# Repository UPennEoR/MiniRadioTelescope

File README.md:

# Mini Radio Telescope

A computerized telescope created using a satellite TV dish and hobbyist electronic components.<br/>
This GitHub contains Arduino and Python code for the telescope.

## Hardware
### Electronics

* Satellite Dish (with LNB)
* Arduino Uno
* Raspberry Pi
* [Stepper Motors](https://www.sparkfun.com/products/13656)
* [Big Easy Driver](https://www.sparkfun.com/products/12859)

### RF
* [Bias Tee](https://www.minicircuits.com/WebStore/dashboard.html?model=ZFBT-282-1.5A%2B)
* [Lumped LC High Pass Filter, 910 - 3000 MHz](https://www.minicircuits.com/WebStore/dashboard.html?model=SHP-900%2B)
* [LTCC Low Pass Filter, DC - 1200 MHz, 50Ω](https://www.minicircuits.com/WebStore/dashboard.html?model=VLF-1200%2B)
* [Power Detector](https://www.minicircuits.com/WebStore/dashboard.html?model=ZX47-60LN-S%2B)
* [Low Noise Amplifier, 40 - 2600 MHz, 50Ω](https://www.minicircuits.com/WebStore/dashboard.html?model=ZX60-P105LN%2B)
* [RTL-SDR](https://www.amazon.com/RTL-SDR-Blog-RTL2832U-Software-Defined/dp/B0129EBDS2/)

[Detailed Parts List](https://docs.google.com/spreadsheets/d/1V9u7jmuFzU5uZdgKm3iKv23dL2x4DQUVWW0j8lXsqZ8/edit?usp=sharing)

## Maps

As of 5 April 2020, the working Arduino sketch is: MRTArduino (previously known as MRTv2)<br/>
The python code for the Pi is MRT_PY4.py

Hackaday was kind enough to do a write-up about this project: https://hackaday.com/2019/10/22/a-miniature-radio-telescope-in-every-backyard/

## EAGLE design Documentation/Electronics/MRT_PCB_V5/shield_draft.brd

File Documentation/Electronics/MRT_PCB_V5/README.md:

The zip file is appropriate for PCB4U.

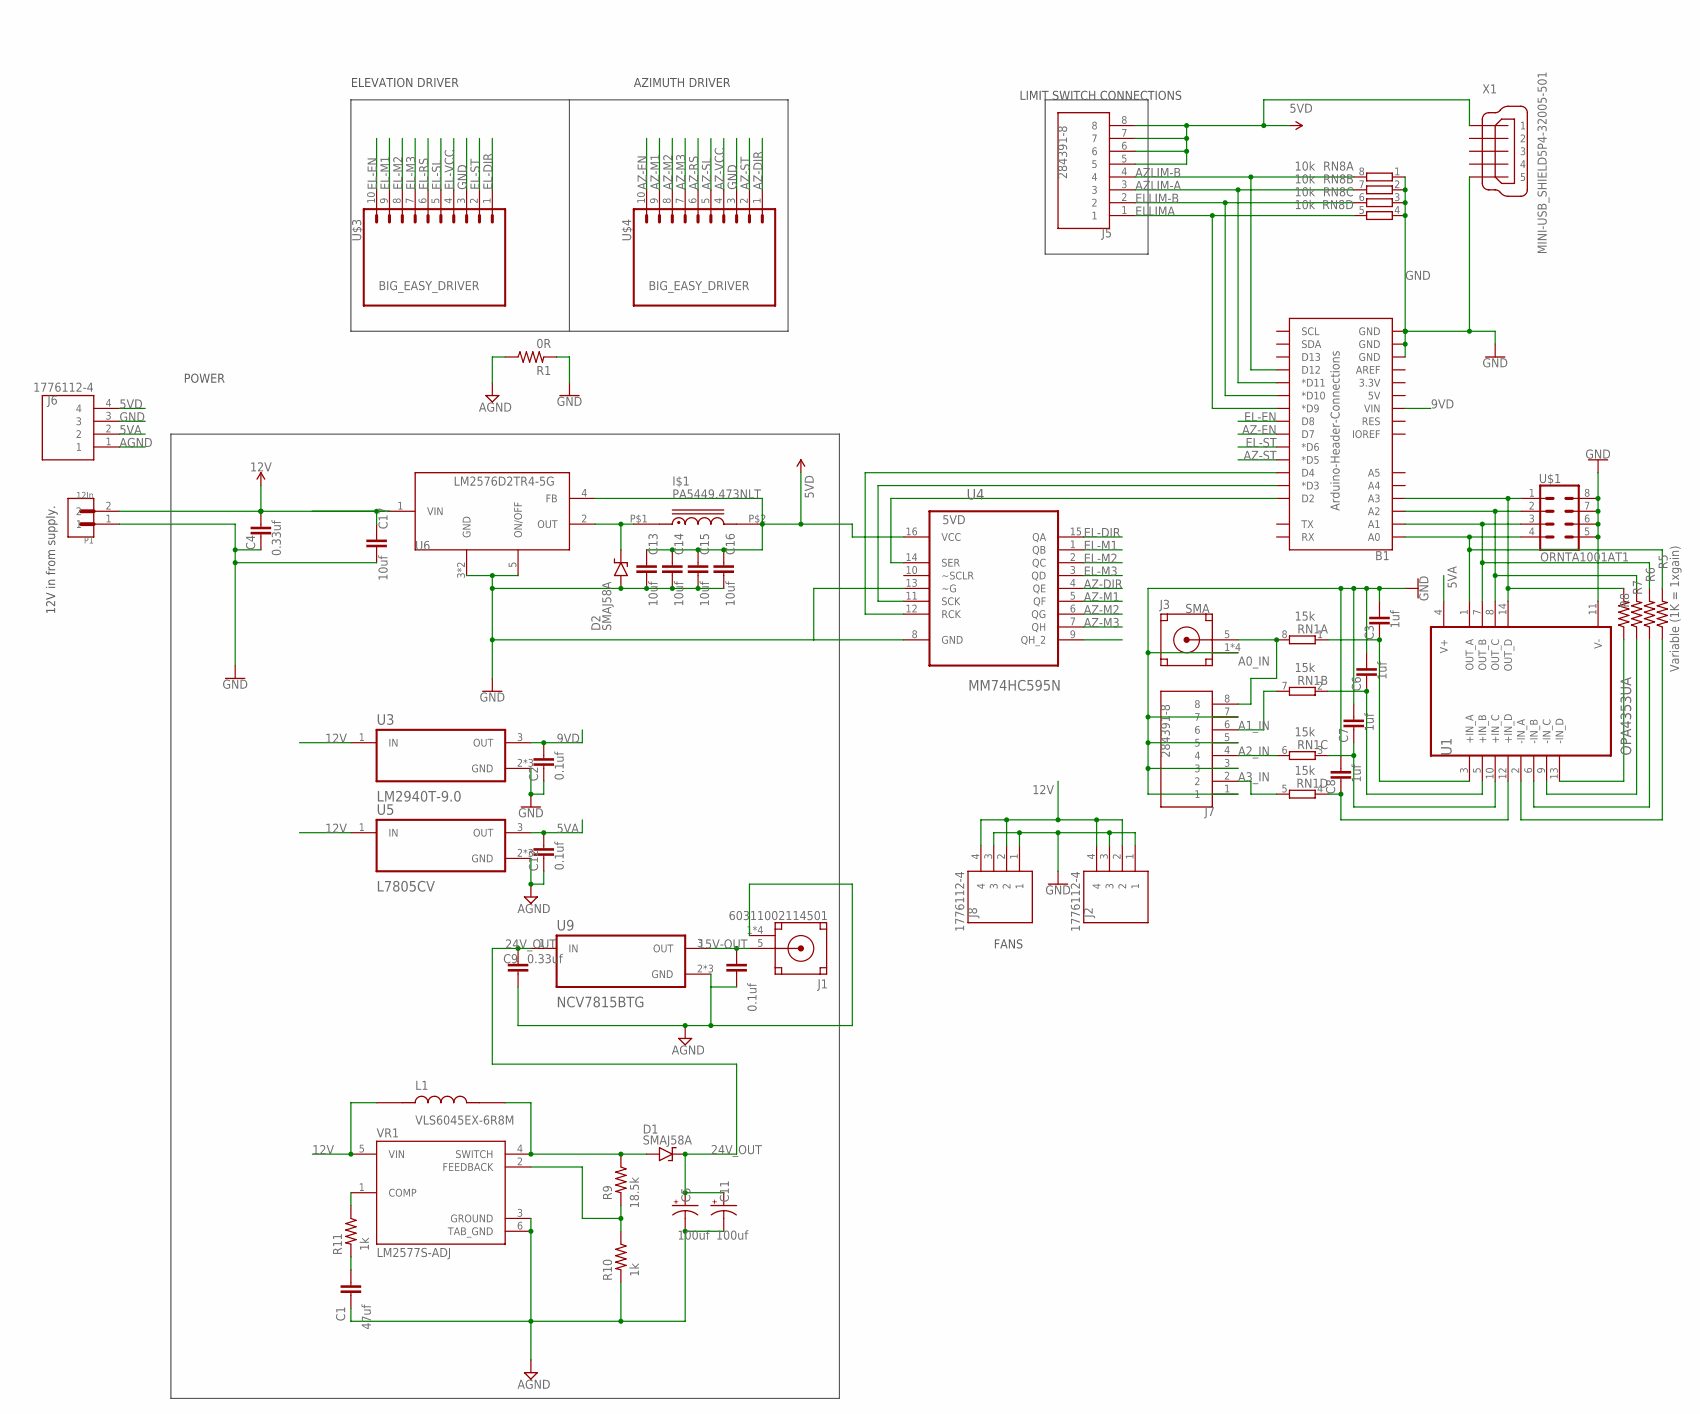
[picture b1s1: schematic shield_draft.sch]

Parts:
B1: Arduino-Header-Connections; UNO_R3_SHIELD
C1: 47uf; CAP_0805
C2, C10, C12: 0.1uf; CAP_0805
C3, C6, C7, C8: 1uf; CAP_0805
C4, C9: 0.33uf; CAP_0805
C5, C11: 100uf; E5-10,5
C13, C14, C15, C16, C17: 10uf; 0805
D1, D2: SMAJ58A; SMA
I$1: PA5449.473NLT; IND_TYS4020470M-10
J1: 60311002114501
J2, J6, J8: 1776112-4; TE_1776112-4
J3: SMA; 60311002114501
J5, J7: 284391-8; TE_284391-8
L1: VLS6045EX-6R8M; IND_VLS6045EX-6R8M
P1: 12In; OST_OSTTE020104
R1: 0R; 0603
R5: Variable (1K = 1xgain); RESAD1176W63L850D250B
R6, R7, R8: Var; RESAD1176W63L850D250B
R9: 18.5k; 0603
R10, R11: 1k; 0603
RN1: 15k; CAY16
RN8: 10k; CAY16
U1: OPA4353UA; SOIC127P600X175-14N
U3: LM2940T-9.0; TO254P1054X470X1955-3
U4: MM74HC595N; DIP254P762X533-16
U5: L7805CV; TO254P1054X470X1955-3
U6: LM2576D2TR4-5G; D2PAK-5
U9: NCV7815BTG; TO254P1054X470X1955-3
U$1: ORNTA1001AT1; SOIC127P600X175-8N
U$3, U$4: BIG_EASY_DRIVER; EASY_DRIVER_FTPRT
VR1: LM2577S-ADJ; TO170P1524X483-6N
X1: MINI-USB_SHIELD5P4-32005-501; 32005-501

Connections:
5VA: C12.2, J6.2, U1.4 (V+), U5.3 (OUT)
5VD: C13.1, C14.1, C15.1, C16.1, I$1.P$2 (2), J5.5, J5.6, J5.7, J5.8, J6.4, U4.16 (VCC), U6.4 (FB), X1.1
9VD: B1.VIN, C2.2, U3.3 (OUT)
12V: C4.2, C17.1, J2.2, J2.4, J8.2, J8.4, L1.1, P1.2, U3.1 (IN), U5.1 (IN), U6.1 (VIN), VR1.5 (VIN)
15V-OUT: C10.2, J1.5 (SIGNAL), U9.3 (OUT)
24V_OUT: C5.+, C9.2, C11.+, D1.C, U9.1 (IN)
24V_PRE: D1.A, L1.2, R9.1, VR1.4 (SWITCH)
A0_IN: J3.5 (SIGNAL), J7.8, RN1.8 (2)
A1_IN: J7.6, RN1.7 (2)
A2_IN: J7.4, RN1.6 (2)
A3_IN: J7.2, RN1.5 (2)
AGND: C1.1, C5.-, C9.1, C10.1, C11.-, C12.1, J1.1 (GND), J1.2 (GND), J1.3 (GND), J1.4 (GND), J6.1, R1.1, R10.2, U5.2 (GND), U5.P$1 (GND), U5.P$2 (GND), U9.2 (GND), U9.P$1 (GND), U9.P$2 (GND), VR1.3 (GROUND), VR1.6 (TAB_GND)
AIN+: C3.1, RN1.1, U1.3 (+IN_A)
AIN-: R5.1, U1.2 (-IN_A)
AZ-DIR: U4.4 (QE), U$4.1
AZ-EN: B1.D7, U$4.10
AZ-M1: U4.5 (QF), U$4.9
AZ-M2: U4.6 (QG), U$4.8
AZ-M3: U4.7 (QH), U$4.7
AZ-RS: U$4.6
AZ-SL: U$4.5
AZ-ST: B1.D5 (*D5), U$4.2
AZ-VCC: U$4.4
AZLIM-A: B1.D11 (*D11), J5.3, RN8.7 (2)
AZLIM-B: B1.D12, J5.4, RN8.8 (2)
A_OUT: B1.A0, R5.2, U1.1 (OUT_A), U$1.4 (R4A)
BIN+: C6.1, RN1.2 (1), U1.5 (+IN_B)
BIN-: R6.1, U1.6 (-IN_B)
B_OUT: B1.A1, R6.2, U1.7 (OUT_B), U$1.3 (R3A)
CIN+: C7.1, RN1.3 (1), U1.10 (+IN_C)
CIN-: R7.1, U1.9 (-IN_C)
C_OUT: B1.A2, R7.2, U1.8 (OUT_C), U$1.2 (R2A)
DIN+: C8.1, RN1.4 (1), U1.12 (+IN_D)
DIN-: R8.1, U1.13 (-IN_D)
D_OUT: B1.A3, R8.2, U1.14 (OUT_D), U$1.1 (R1A)
EL-DIR: U4.15 (QA), U$3.1
EL-EN: B1.D8, U$3.10
EL-M1: U4.1 (QB), U$3.9
EL-M2: U4.2 (QC), U$3.8
EL-M3: U4.3 (QD), U$3.7
EL-RS: U$3.6
EL-SL: U$3.5
EL-ST: B1.D6 (*D6), U$3.2
EL-VCC: U$3.4
ELLIM-B: B1.D10 (*D10), J5.2, RN8.6 (2)
ELLIMA: B1.D9 (*D9), J5.1, RN8.5 (2)
GND: B1.GND@0 (GND), B1.GND@1 (GND), B1.GND@2 (GND), C2.1, C3.2, C4.1, C6.2, C7.2, C8.2, C13.2, C14.2, C15.2, C16.2, C17.2, D2.A, J2.1, J2.3, J3.1 (GND), J3.2 (GND), J3.3 (GND), J3.4 (GND), J6.3, J7.1, J7.3, J7.5, J7.7, J8.1, J8.3, P1.1, R1.2, RN8.1, RN8.2 (1), RN8.3 (1), RN8.4 (1), U1.11 (V-), U3.2 (GND), U3.P$1 (GND), U3.P$2 (GND), U4.8 (GND), U4.13 (~G), U6.3 (GND), U6.5 (ON/OFF), U6.6 (GND), U$1.5 (R4B), U$1.6 (R3B), U$1.7 (R2B), U$1.8 (R1B), U$3.3, U$4.3, X1.5
unnamed: B1.D2, U4.14 (SER)
unnamed: R9.2, R10.1, VR1.2 (FEEDBACK)
unnamed: D2.C, I$1.P$1 (1), U6.2 (OUT)
unnamed: R11.1, VR1.1 (COMP)
unnamed: C1.2, R11.2
unnamed: B1.D3 (*D3), U4.11 (SCK)
unnamed: B1.D4, U4.12 (RCK)

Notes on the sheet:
POWER
ELEVATION DRIVER
AZIMUTH DRIVER
LIMIT SWITCH CONNECTIONS
12V in from supply.
FANS

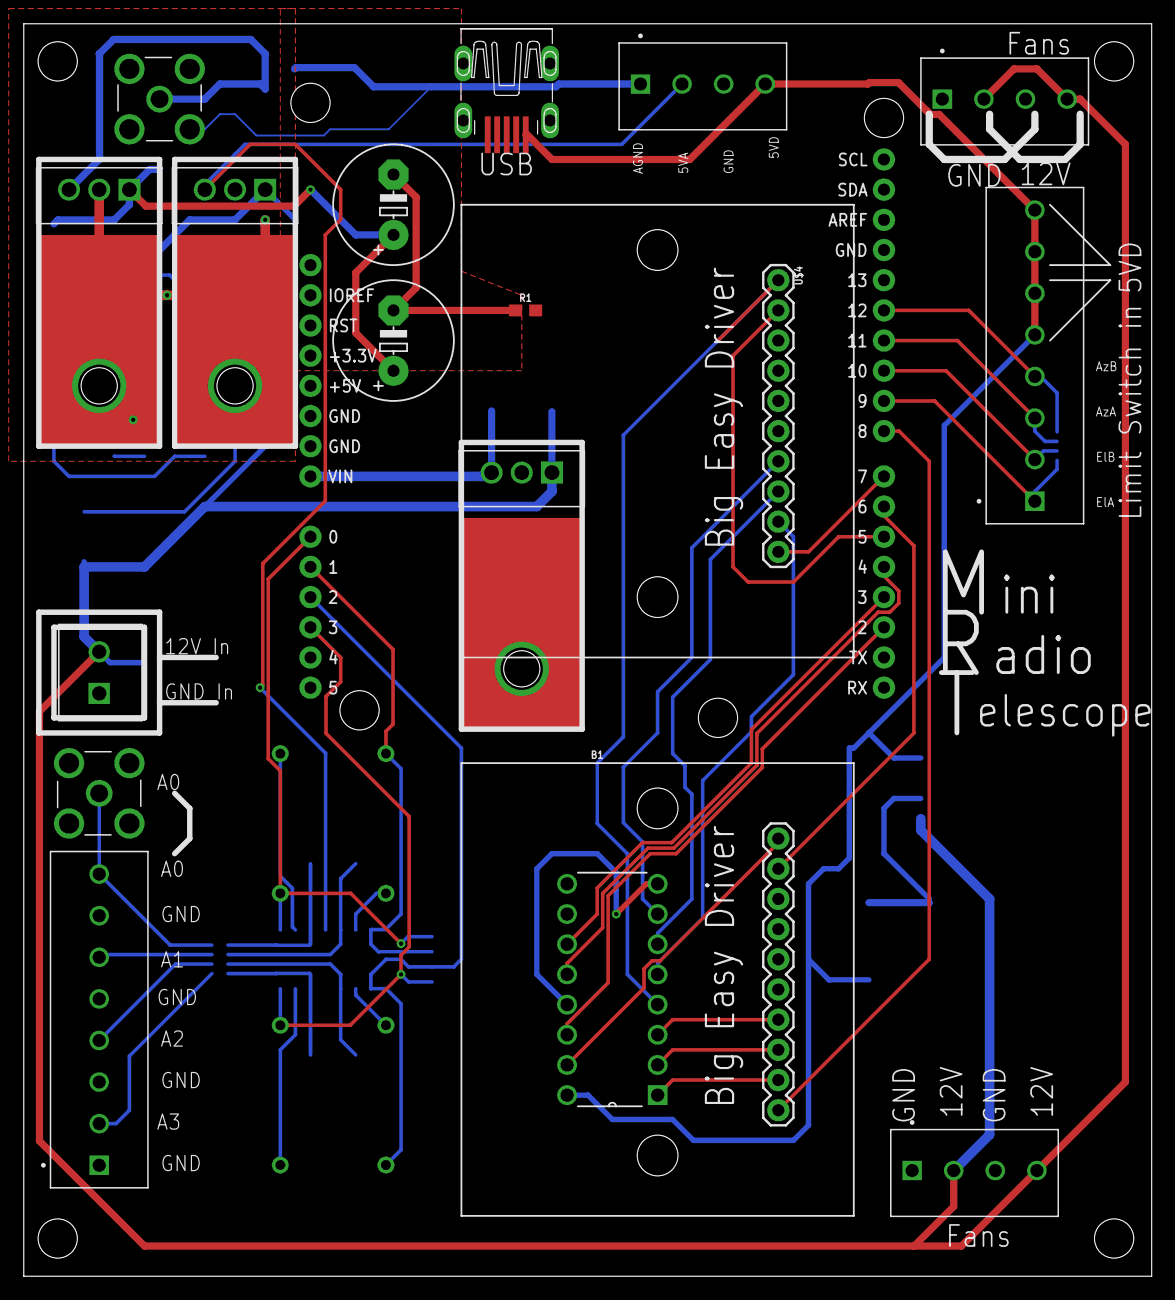
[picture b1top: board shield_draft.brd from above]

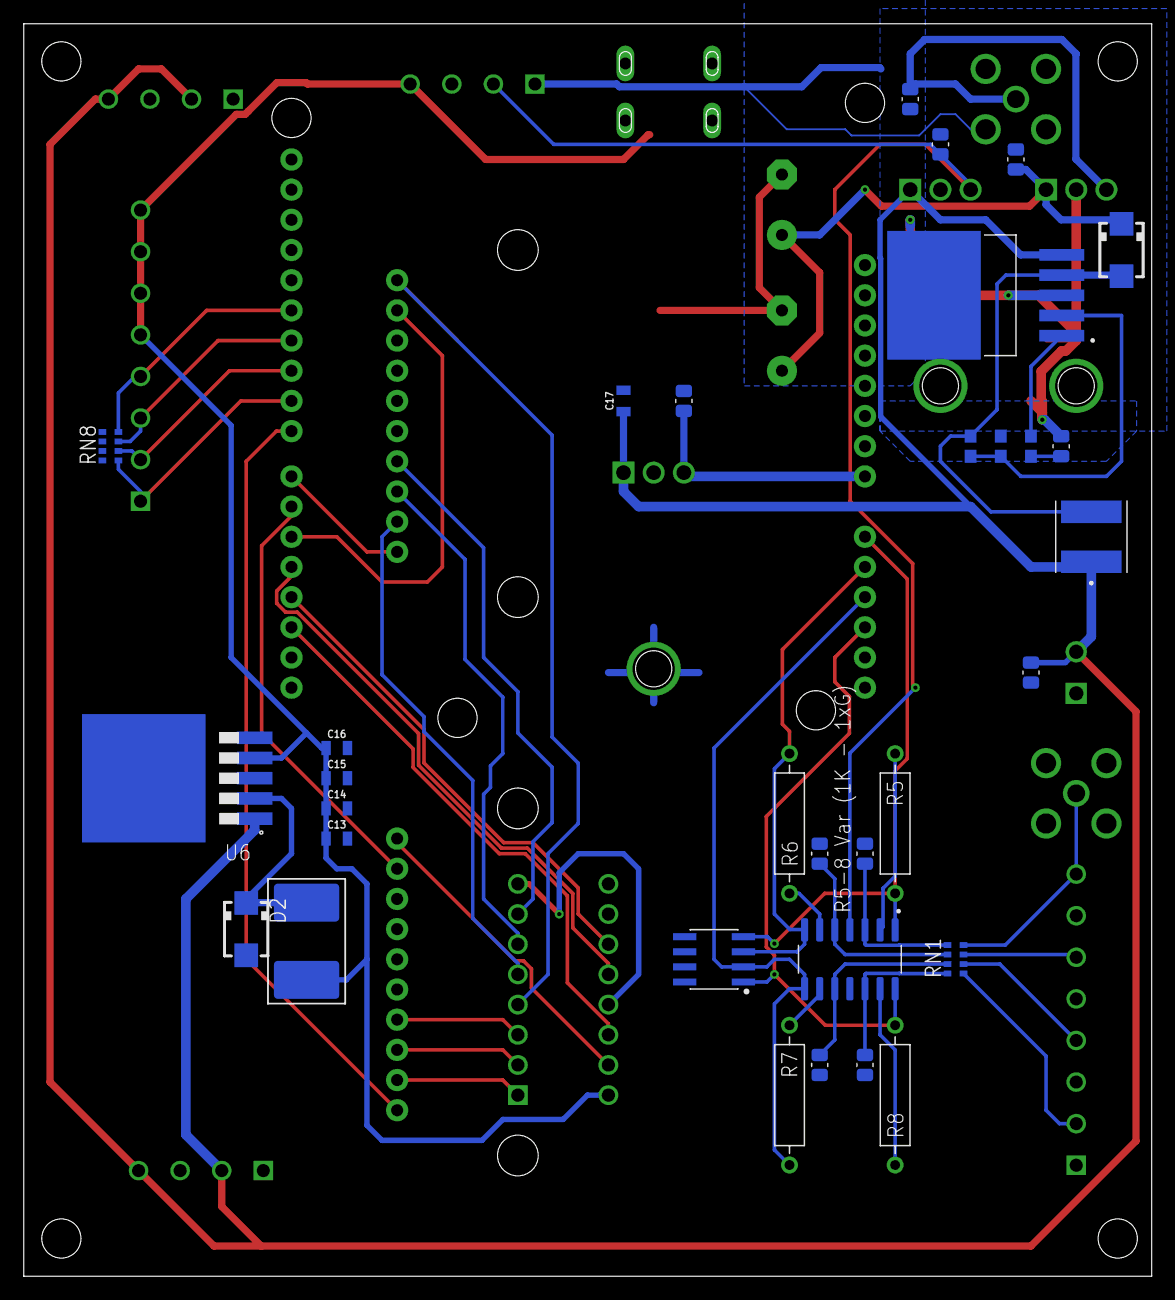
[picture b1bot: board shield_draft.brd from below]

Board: 2 copper layers, 94.9 x 105.4 mm, 59 parts (32 on the bottom side), 48 nets.

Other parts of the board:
JP1, JP2, JP3, JP4, JP5, JP6, JP7, JP10: STAND-OFF

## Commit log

2016-07-15 Arduino code for the LMS9DS1 sensor and separately for motor control
2016-07-18 Real time plotting
2016-07-18 Trying to make a python version of the Arduino serial monitor
2016-07-20 pyArduinoSerialTerminal.py basically reproduces the Arduino Serial Monitor functionality now, though there is a bit of an offset between when the Arduino sends something to the buffer and this progra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
2016-07-29 Serial communication
2016-07-29 A serial communication tester for Arduino
2016-07-29 Working simple serial communication with Arduino
2016-08-10 Making the Arduino stuff more organized
2016-08-10 One more Arduino ino
2016-08-10 Pseudo-working Arduino and Python serial
2016-08-15 added a test of handshaking
2016-08-16 handshaking example
2016-08-26 serial communication now working with Pi
2016-12-14 Adding some documentation
2016-12-14 Current working version
2017-02-09 Thu Feb 9 16:56:14 EST 2017
2017-02-09 unbroken version
2017-03-01 Wed Mar 1 14:04:58 EST 2017
2017-03-01 Wed Mar 1 17:38:22 EST 2017
2017-03-03 Fri Mar 3 10:53:11 EST 2017
2017-03-28 Tue Mar 28 00:14:23 EDT 2017
2017-04-01 Sat Apr 1 10:40:33 EDT 2017
2017-06-21 Wed Jun 21 14:34:22 EDT 2017
2017-06-30 Fri Jun 30 14:20:31 EDT 2017
2017-06-30 Fri Jun 30 14:43:24 EDT 2017
2017-06-30 Fri Jun 30 14:46:32 EDT 2017
2017-07-05 Wed Jul 5 10:19:24 EDT 2017
2017-07-07 Fri Jul 7 15:49:47 EDT 2017
2017-07-07 Fri Jul 7 15:54:09 EDT 2017
2017-07-09 Sun Jul 9 14:03:56 EDT 2017
2017-07-18 Tue Jul 18 13:09:20 EDT 2017
2017-07-28 Fri Jul 28 11:50:43 EDT 2017
2017-08-01 Notes on Pi3 installation
2017-08-07 Installation instructions
2017-08-07 rtlsdr_scan.py
2017-08-08 Tue Aug 8 16:58:33 EDT 2017
2017-08-08 Tue Aug 8 17:03:22 EDT 2017
2017-08-09 Shell script way of starting MRTControl.py
2017-08-09 Wed Aug 9 09:54:37 EDT 2017
2017-08-09 Wed Aug 9 11:14:17 EDT 2017
2017-08-09 Wed Aug 9 11:16:30 EDT 2017
2017-08-09 An example SDR spectrum
2017-08-10 Wed Aug 9 21:29:55 EDT 2017
2017-10-12 Thu Oct 12 16:13:34 EDT 2017
2017-10-26 Committing.
2017-11-17 Adding a new version of the MRT software
2017-11-17 Fri Nov 17 17:44:08 EST 2017
2017-11-17 Fri Nov 17 18:33:53 EST 2017
2017-11-17 Fri Nov 17 18:43:14 EST 2017
2017-11-27 Mon Nov 27 02:38:42 EST 2017
2017-12-03 Sun Dec 3 11:36:05 EST 2017
2017-12-04 Mon Dec 4 01:33:33 EST 2017
2017-12-04 Mon Dec 4 11:17:35 EST 2017
2017-12-04 Mon Dec 4 11:25:31 EST 2017
2017-12-04 Mon Dec 4 18:47:03 EST 2017
2018-01-16 Tue Jan 16 10:54:02 EST 2018
2018-04-04 Wed Apr 4 09:42:31 EDT 2018
2018-04-04 Wed Apr 4 09:58:07 EDT 2018
2018-04-04 Wed Apr 4 11:13:50 EDT 2018
2018-04-11 Wed Apr 11 13:49:21 EDT 2018
2018-04-12 Thu Apr 12 12:15:35 EDT 2018
2018-04-27 Fri Apr 27 19:12:53 EDT 2018
2018-04-28 Fri Apr 27 20:41:38 EDT 2018
2018-04-28 Fri Apr 27 20:52:47 EDT 2018
2018-05-14 Mon May 14 15:30:04 EDT 2018
2018-06-11 Adding PCRT design document
2018-06-13 Made a new version for a python3 compatible MRT.py
2018-06-14 should be working
2018-06-15 Fri Jun 15 12:29:36 EDT 2018
2018-06-15 Fri Jun 15 12:35:22 EDT 2018
2018-06-15 Trying to get satellites with MRT
2018-06-15 Getting them satellites
2018-06-15 Adding maps
2018-06-15 the maps
2018-06-19 Tuesday June 19 update
2018-06-19 the maps 2
2018-07-03 All mrt functions
2018-07-03 temporary MRT PY3 to sort functions into a new file
2018-07-03 new file containing information on the state of the telescope
2018-07-03 New file containing just the opening for the program from opening the port to initializing the state
2018-07-03 test file for mrt func, doesn't contain every function that func does
2018-07-06 seems to be working, no longer producesnone type nonsubscriptable error
2018-07-06 also seems to be working, about to input while loop that runs MRT
2018-07-06 holds the state
2018-07-06 funcional by itself, but having problems in tandem with FUNC
2018-07-06 Fully functional up to the GoTo function
2018-07-09 Almost fully functional, just need to work out the bugs caused by the mapping funcions in FUNC
2018-07-09 WE ARE SO CLOSE! Just need to work on the bugs in mapping functions to accomodate changes in how scan and goto and state work
2018-07-12 Everything seems to be functional, just cleaning up a bit and adding features now.
2018-07-12 Fully functional
2018-07-12 fully functional now, but the official program is MRT_PY3.py which is the same as this one.
2018-07-12 Finally no bugs, works great.
2018-07-12 Fully functional with some new modifications, including variable dimensions in mapping and a print menu function.
2018-07-12 Still fully functional, just working on cleaning up the figures produced by the mapping functions.
2018-07-16 added some stuff, cleaned up the code, and added comments to everything for better understanding
2018-07-16 Nothing new, just a little cleaner.
2018-07-23 A few tweeks and things including approximate time to completion for RasterMap
2019-04-27 Sat Apr 27 01:01:03 EDT 2019
2019-05-14 Tue May 14 15:21:12 EDT 2019
2019-07-18 Wed Jul 17 20:46:58 EDT 2019
2019-07-18 Wed Jul 17 20:54:27 EDT 2019
2019-07-18 Wed Jul 17 20:55:09 EDT 2019
2019-07-18 Wed Jul 17 20:55:45 EDT 2019
2019-07-18 Wed Jul 17 20:57:07 EDT 2019
2019-07-18 Wed Jul 17 20:58:16 EDT 2019
2019-07-18 Wed Jul 17 21:01:39 EDT 2019
2019-07-18 Wed Jul 17 21:02:56 EDT 2019
2019-07-18 Wed Jul 17 21:04:14 EDT 2019
2019-07-18 Wed Jul 17 21:17:53 EDT 2019
2019-07-18 Wed Jul 17 21:50:04 EDT 2019
2019-07-20 Make python3 compliant
2019-07-23 Mon Jul 22 22:56:04 EDT 2019
2019-07-23 Mon Jul 22 22:56:52 EDT 2019
2019-07-23 Mon Jul 22 22:57:24 EDT 2019
2019-08-15 Changes made during EPRA
2019-08-23 new software post EPRA
2019-09-30 New changes to the MRT software
2019-09-30 Spectral scan stuff
2019-10-05 Sat Oct 5 14:04:47 EDT 2019
2019-10-05 Sat Oct 5 14:07:49 EDT 2019
2019-10-05 Sat Oct 5 14:07:56 EDT 2019
2019-10-05 Sat Oct 5 14:52:25 EDT 2019
2019-11-03 Sun Nov 3 17:28:12 EST 2019
2019-11-03 Sun Nov 3 17:28:19 EST 2019
2019-11-03 Sun Nov 3 17:28:40 EST 2019
2019-11-13 Added Sample Scan and Map Plots
2019-11-20 Majority of GUI is in place. Telescope control code from MRT_PY4, MRT_FUNC_PY4, and mrtstate added. Buttons don't do anything just yet.
2019-11-26 Added Commands from MRT_PY4.py
2020-02-09 Sun Feb 9 03:12:37 EST 2020
2020-02-09 Sun Feb 9 03:13:06 EST 2020
2020-02-09 Sun Feb 9 03:13:17 EST 2020
2020-03-03 Fixed non-ASCII strings
2020-03-04 Committing from Pi
2020-03-04 Main checkout push
2020-03-04 some fixes to tkcanvas and non-ASII characters; now runs on Pi
2020-03-05 Thu Mar 5 09:29:59 EST 2020
2020-03-05 Thu Mar 5 09:33:40 EST 2020
2020-03-05 Thu Mar 5 09:37:44 EST 2020
2020-03-05 Thu Mar 5 09:39:45 EST 2020
2020-03-05 Thu Mar 5 09:46:00 EST 2020
2020-03-05 Thu Mar 5 09:48:47 EST 2020
2020-03-05 Thu Mar 5 10:01:36 EST 2020
2020-03-05 Thu Mar 5 10:08:47 EST 2020
2020-03-05 Thu Mar 5 10:14:18 EST 2020
2020-03-05 Thu 05 Mar 2020 10:21:45 AM EST
2020-03-31 Created new Arduino code based on CNC G-Code. To be used for code development without telescope hardware.
2020-06-04 Started integrating back end control of telescope. Added map support.
2020-06-05 Started integrating back end control of telescope. Added scan support.
2020-07-03 Added setpoint control.
2020-07-03 Added quick move.
2020-07-06 Small bug fixes, refresh button for current readings, started working on connecting the Arduino
2020-07-11 Auto find of Arduino port and connection.
2020-07-29 Wed Jul 29 15:48:40 EDT 2020
2020-08-06 Matched mrtstate with Arduino code. Moved serial to main program and changed FUNC to match.
2020-08-06 Scanning through GUI now works. Live update of graph not yet.
2020-08-28 Fri Aug 28 15:44:01 EDT 2020
2020-08-28 Fri Aug 28 15:44:09 EDT 2020
2020-08-28 Fri Aug 28 15:44:16 EDT 2020
2021-02-16 bringing things up to date
2021-02-16 Making directory name conform to Arduino convention
2021-03-15 Newer, better, cheaper
2021-03-15 Latest
2021-03-15 some changes on STARFIRE
2021-03-31 Wed Mar 31 12:36:45 EDT 2021
2021-03-31 Wed Mar 31 12:37:05 EDT 2021
2021-04-19 Mon Apr 19 00:33:27 EDT 2021
2021-04-19 Mon Apr 19 00:33:36 EDT 2021
2021-04-19 Mon Apr 19 00:33:49 EDT 2021
2021-04-19 Mon Apr 19 00:35:44 EDT 2021
2021-04-19 Mon Apr 19 00:35:51 EDT 2021
2021-04-19 Mon Apr 19 15:40:17 EDT 2021
2021-05-27 Thu May 27 12:29:03 EDT 2021
2021-07-21 Wed Jul 21 07:01:38 EDT 2021
2021-07-21 Wed Jul 21 07:47:15 EDT 2021
2022-02-07 adding the PCB schematics
2023-01-27 Delete Plots directory
    There are a lot of files with illegal file name symbols in them. Primarily ":"
2023-01-27 switched huge if elif chain for match case
2023-02-06 Clean up
2023-02-19 TrackedObject class for getting local alt az by star name
2025-03-27 Trying to fix : in name problem
2025-03-27 Fixing the : problem
2025-03-28 dear god why?
2025-03-28 really?
2025-04-19 Once more unto the breach
2025-04-19 Sisyphus

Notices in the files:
parts and their libraries:
SparkFun-Boards: Licensing: Creative Commons ShareAlike 4.0 International - https://creativecommons.org/licenses/by-sa/4.0
